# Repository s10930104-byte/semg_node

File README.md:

Phase 1：需求收斂與競品拆解（本週優先）
明確定義系統需求：確立量測應用場景、通道數、取樣率、電池容量與目標續航時間，作為後續元件選型的唯一依據。

競品採購與拆解參考：視需求採購市售同類模組（如淘寶現成方案）進行拆解，分析其晶片配置與機構空間規劃（註：僅作架構參考，須依自身專案用途篩選，避免盲目照抄）。

Phase 2：核心硬體架構定案（MCU / BLE / IMU）
MCU 與 BLE 架構拍板：依運算需求與功耗預算，決定採用「BLE SoC 單晶片方案」或「獨立 MCU + 獨立 BLE 模組」。

通訊介面與腳位盤點 (Pinout)：確認 MCU 具備足夠通道數與硬體協議（SPI / I2C / UART / SWD），確保能同時掛載 ADS1292、IMU 與燒錄除錯介面而不衝突。

IMU 感測器選型：確認慣性測量單元型號與通訊介面（SPI 或 I2C），完成硬體規格鎖定（韌體演算法待硬體定案後再行開發）。

Phase 3：電源管理與類比前端規劃（Power & AFE）
電源控制器與 S0–S5 狀態機設計：選定 PMIC / 充放電管理 IC，並定義 S0（全速運作）至 S5（完全關機斷電）各階段的供電策略與喚醒條件。

LDO 電源軌配置 (Power Tree)：

規劃 小電流低雜訊 LDO 專供類比前端（ADS1292），確保訊號品質。

規劃 大電流 LDO 供應數位主控與 IMU 等高功耗周邊。

確認其餘次要邏輯電源直接沿用 BLE 模組內建 LDO（若 Phase 2 改採單晶片方案則統一由上述兩顆分配）。

ADS1292 前端防護修改：將輸入端靜電保護（ESD）改為類比訊號專用規格（低漏電流、低寄生電容），避免影響微弱生理訊號。

Phase 4：機構介面與人機互動確認（開板前 Final Check）
雙模式電極介面定案：

確認板端/外殼乾式電極接觸點配置。

選定外接導線 Connector 規格，支援拉線外接標準貼片式 ECG/EMG 電極。

自定義按鍵 (User Button) 配置：預留實體按鍵並接至具備中斷喚醒功能的 MCU GPIO，供後期韌體自定義功能（開關機、配對、事件標記等）。

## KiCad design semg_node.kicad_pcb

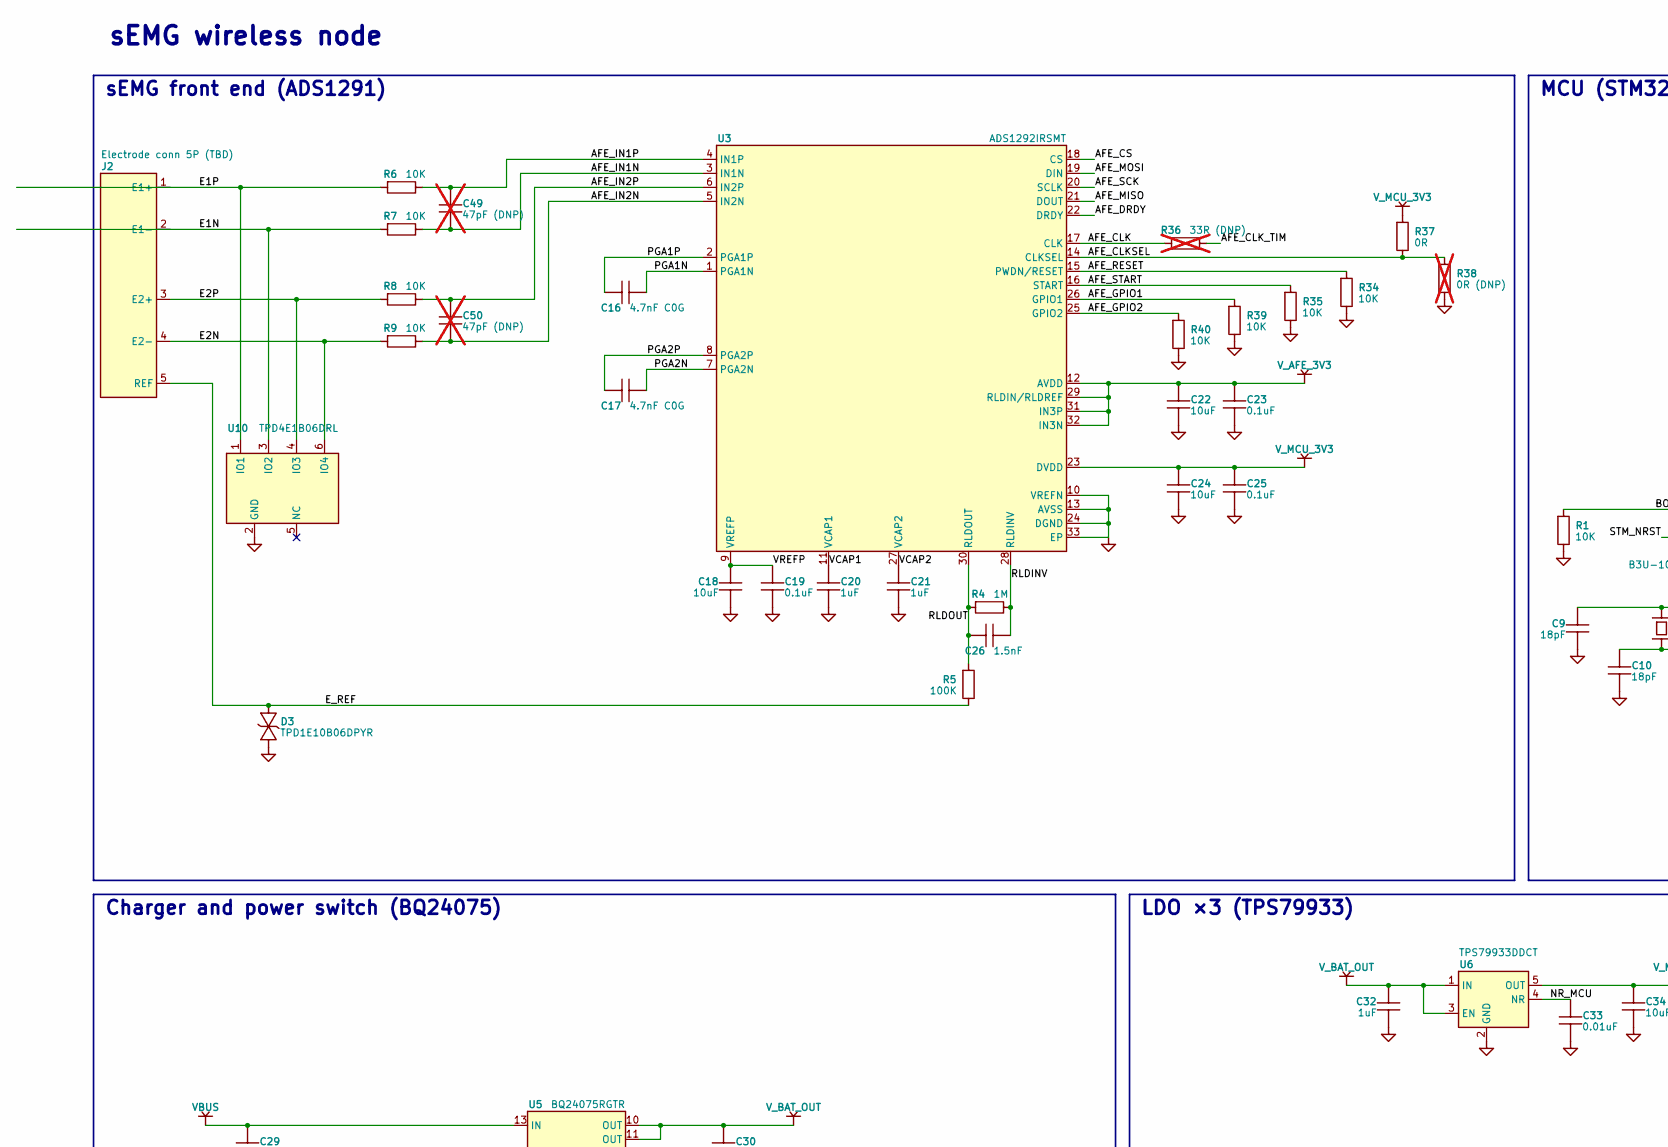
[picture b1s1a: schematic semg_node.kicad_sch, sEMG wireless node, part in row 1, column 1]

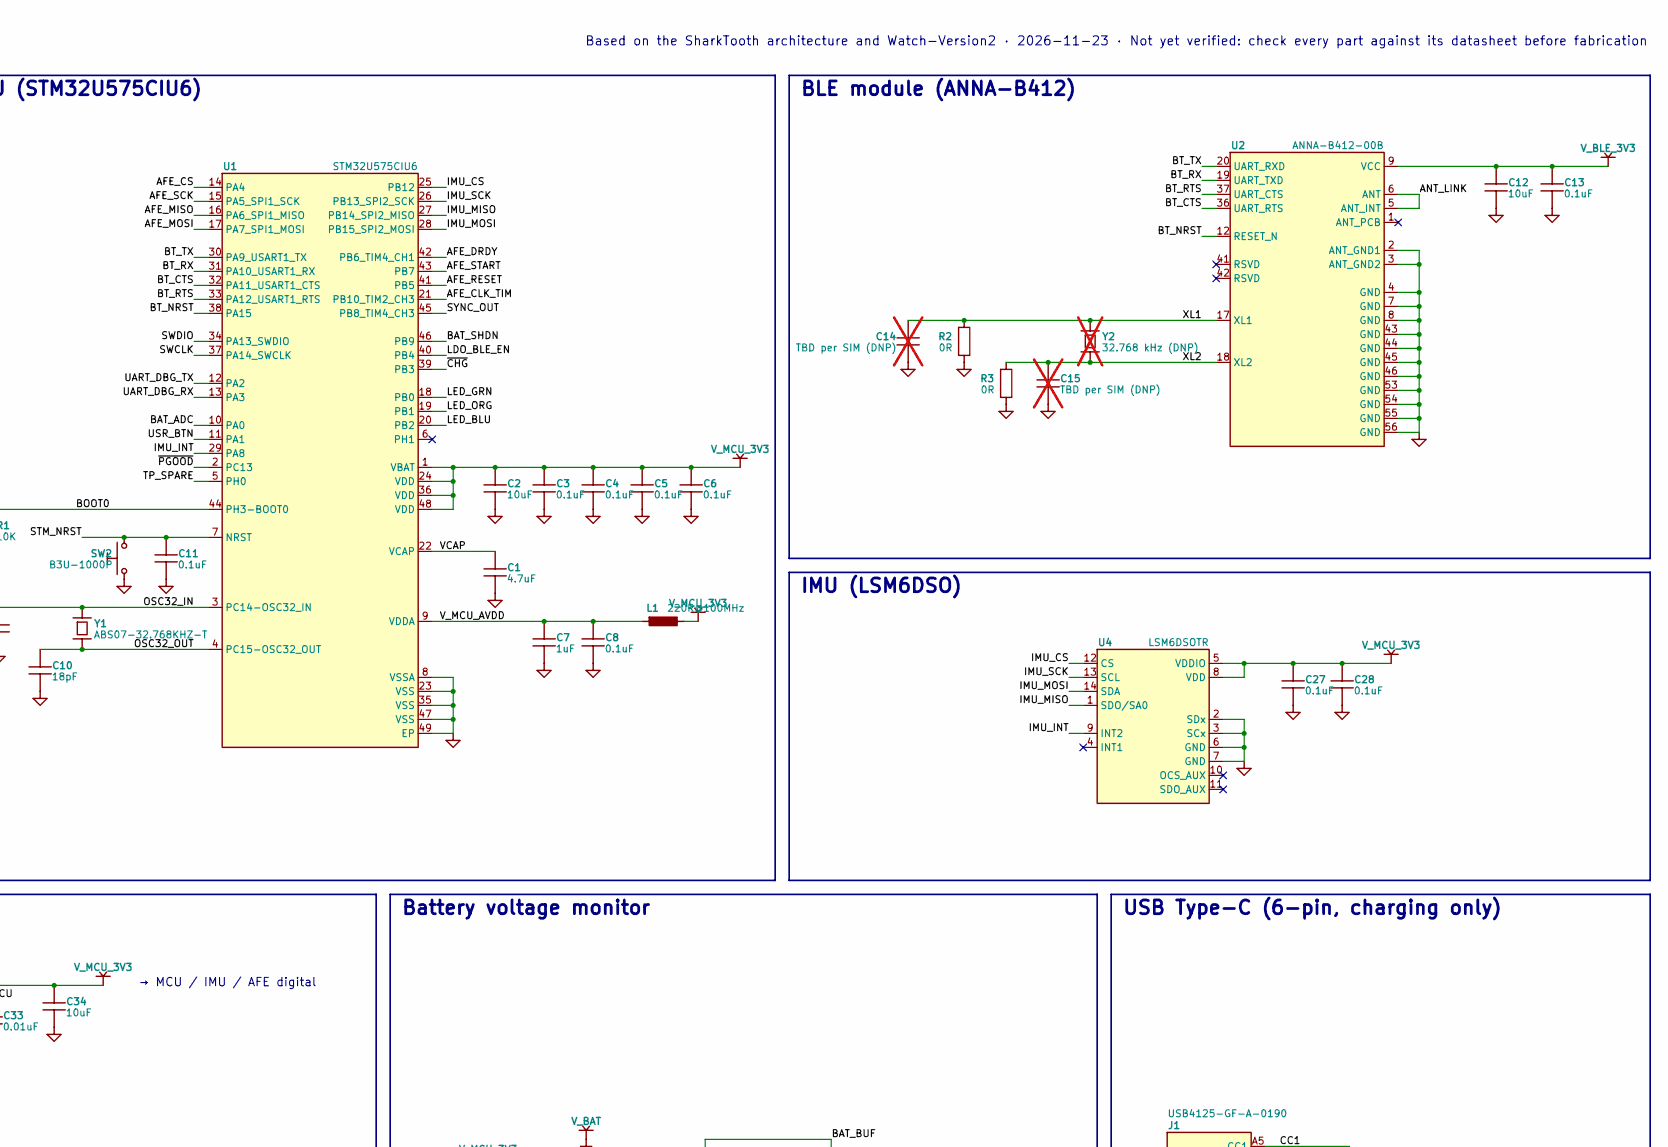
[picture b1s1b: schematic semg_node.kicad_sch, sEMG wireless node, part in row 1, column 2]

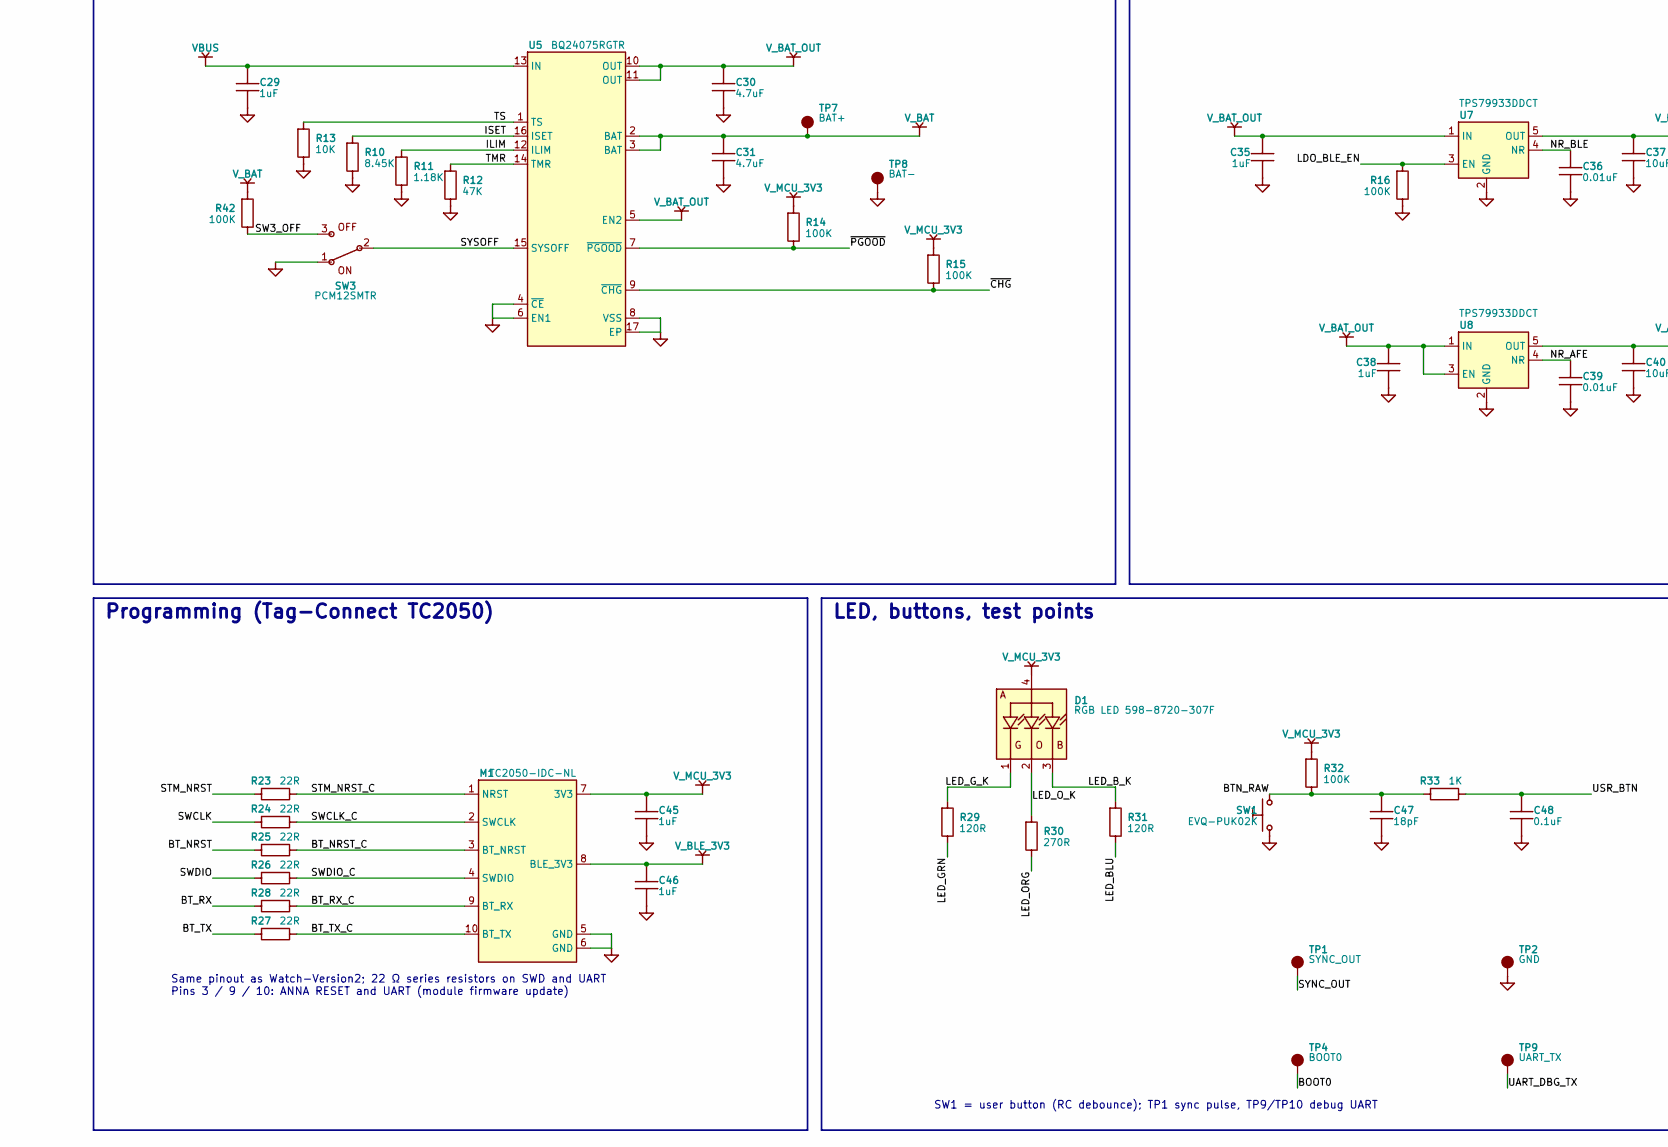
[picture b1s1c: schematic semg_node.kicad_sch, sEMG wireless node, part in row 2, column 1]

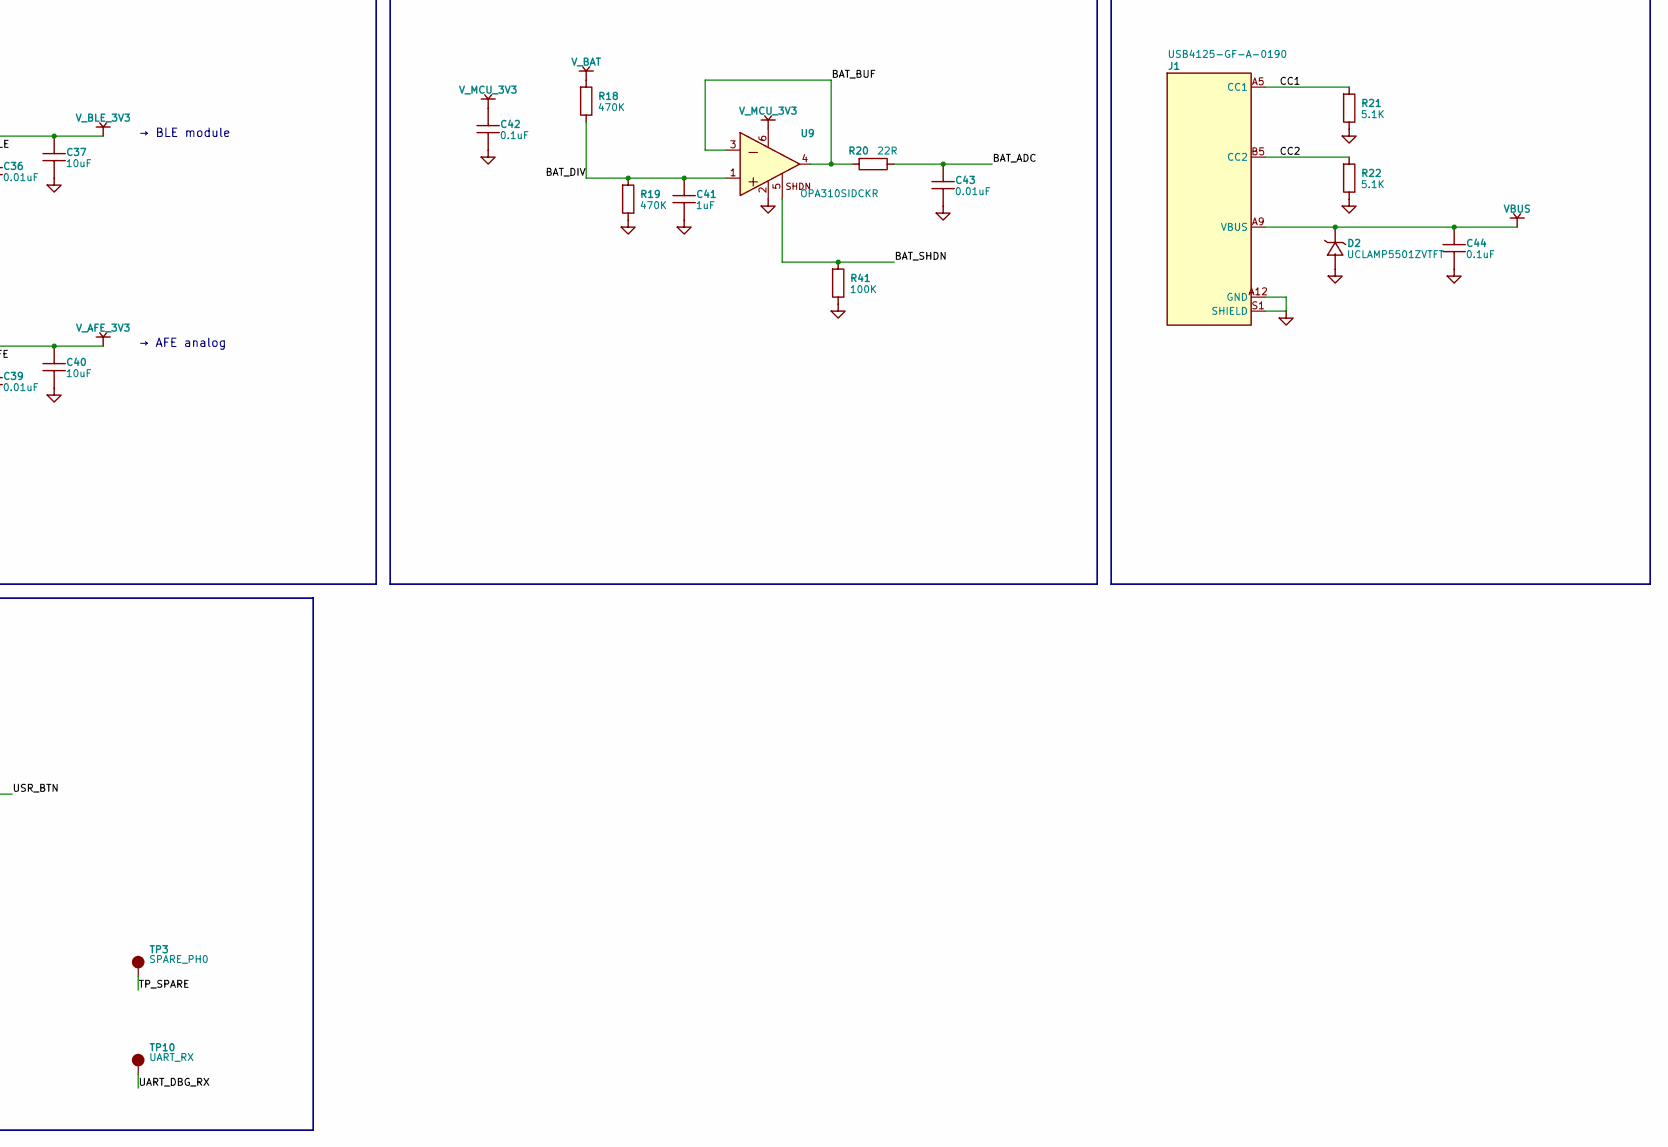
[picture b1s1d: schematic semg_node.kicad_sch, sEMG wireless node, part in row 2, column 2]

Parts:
C1, C30, C31: 4.7uF; C_0603_1608Metric
C2, C12, C18, C22, C24, C34, C37, C40: 10uF; C_0603_1608Metric
C3, C4, C5, C6, C8, C11, C13, C19, C23, C25, C27, C28, C42, C44, C48: 0.1uF; C_0402_1005Metric
C7, C20, C21, C29, C32, C35, C38, C41, C45, C46: 1uF; C_0402_1005Metric
C9, C10, C47: 18pF; C_0402_1005Metric
C14, C15: TBD per SIM (DNP); C_0402_1005Metric; not fitted
C16, C17: 4.7nF C0G; C_0402_1005Metric
C26: 1.5nF; C_0402_1005Metric
C33, C36, C39, C43: 0.01uF; C_0402_1005Metric
C49, C50: 47pF (DNP); C_0402_1005Metric; not fitted
D1: RGB LED 598-8720-307F; LED_RGB_Wuerth-PLCC4_3.2x2.8mm_150141M173100
D2: UCLAMP5501ZVTFT; D_SOD-882
D3: TPD1E10B06DPYR; D_SOD-882
J1: USB4125-GF-A-0190; USB_C_Receptacle_GCT_USB4125-xx-x-0190_6P_TopMnt_Horizontal
J2: Electrode conn 5P (TBD); JST_SH_SM05B-SRSS-TB_1x05-1MP_P1.00mm_Horizontal
L1: 220R@100MHz; L_0402_1005Metric
M1: TC2050-IDC-NL; Tag-Connect_TC2050-IDC-NL_2x05_P1.27mm_Vertical
R1, R6, R7, R8, R9, R13, R34, R35, R39, R40: 10K; R_0402_1005Metric
R2, R3, R37: 0R; R_0402_1005Metric
R4: 1M; R_0402_1005Metric
R5: 100K; R_0603_1608Metric
R10: 8.45K; R_0402_1005Metric
R11: 1.18K; R_0402_1005Metric
R12: 47K; R_0402_1005Metric
R14, R15, R16, R32, R41, R42: 100K; R_0402_1005Metric
R18, R19: 470K; R_0402_1005Metric
R20, R23, R24, R25, R26, R27, R28: 22R; R_0402_1005Metric
R21, R22: 5.1K; R_0402_1005Metric
R29, R31: 120R; R_0402_1005Metric
R30: 270R; R_0402_1005Metric
R33: 1K; R_0402_1005Metric
R36: 33R (DNP); R_0402_1005Metric; not fitted
R38: 0R (DNP); R_0402_1005Metric; not fitted
SW1: EVQ-PUK02K; Panasonic_EVQPUK_EVQPUB
SW2: B3U-1000P; SW_SPST_B3U-1000P
SW3: PCM12SMTR; SW_SPDT_PCM12
TP1: SYNC_OUT; TestPoint_Pad_D1.0mm
TP2: GND; TestPoint_Pad_D1.0mm
TP3: SPARE_PH0; TestPoint_Pad_D1.0mm
TP4: BOOT0; TestPoint_Pad_D1.0mm
TP7: BAT+; TestPoint_Pad_1.5x1.5mm
TP8: BAT-; TestPoint_Pad_1.5x1.5mm
TP9: UART_TX; TestPoint_Pad_D1.0mm
TP10: UART_RX; TestPoint_Pad_D1.0mm
U1: STM32U575CIU6; QFN-48-1EP_7x7mm_P0.5mm_EP5.6x5.6mm
U2: ANNA-B412-00B
U3: ADS1292IRSMT; VQFN-32-1EP_4x4mm_P0.4mm_EP2.8x2.8mm
U4: LSM6DSOTR; LGA-14_3x2.5mm_P0.5mm_LayoutBorder3x4y
U5: BQ24075RGTR; QFN-16-1EP_3x3mm_P0.5mm_EP1.7x1.7mm
U6, U7, U8: TPS79933DDCT; SOT-23-5
U9: OPA310SIDCKR; SOT-363_SC-70-6
U10: TPD4E1B06DRL; SOT-563
Y1: ABS07-32.768KHZ-T; Crystal_SMD_3215-2Pin_3.2x1.5mm
Y2: 32.768 kHz (DNP); Crystal_SMD_3215-2Pin_3.2x1.5mm; not fitted

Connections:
AFE_CLK: R36.2, U3.17 (CLK)
AFE_CLKSEL: R37.1, R38.1, U3.14 (CLKSEL)
AFE_CLK_TIM: R36.1, U1.21 (PB10_TIM2_CH3)
AFE_CS: U1.14 (PA4), U3.18 (CS)
AFE_DRDY: U1.42 (PB6_TIM4_CH1), U3.22 (DRDY)
AFE_GPIO1: R39.1, U3.26 (GPIO1)
AFE_GPIO2: R40.1, U3.25 (GPIO2)
AFE_IN1N: C49.2, R7.2, U3.3 (IN1N)
AFE_IN1P: C49.1, R6.2, U3.4 (IN1P)
AFE_IN2N: C50.2, R9.2, U3.5 (IN2N)
AFE_IN2P: C50.1, R8.2, U3.6 (IN2P)
AFE_MISO: U1.16 (PA6_SPI1_MISO), U3.21 (DOUT)
AFE_MOSI: U1.17 (PA7_SPI1_MOSI), U3.19 (DIN)
AFE_RESET: R34.1, U1.41 (PB5), U3.15 (PWDN/RESET)
AFE_SCK: U1.15 (PA5_SPI1_SCK), U3.20 (SCLK)
AFE_START: R35.1, U1.43 (PB7), U3.16 (START)
BAT_ADC: C43.1, R20.2, U1.10 (PA0)
BAT_BUF: R20.1, U9.3 (-IN), U9.4 (OUT)
BAT_DIV: C41.1, R18.2, R19.1, U9.1 (+IN)
BAT_SHDN: R41.1, U1.46 (PB9), U9.5 (SHDN)
BOOT0: R1.1, TP4.1, U1.44 (PH3-BOOT0)
BTN_RAW: C47.1, R32.2, R33.1, SW1.2
BT_CTS: U1.32 (PA11_USART1_CTS), U2.36 (UART_RTS)
BT_NRST: R25.1, U1.38 (PA15), U2.12 (RESET_N)
BT_NRST_C: M1.3 (BT_NRST), R25.2
BT_RTS: U1.33 (PA12_USART1_RTS), U2.37 (UART_CTS)
BT_RX: R28.1, U1.31 (PA10_USART1_RX), U2.19 (UART_TXD)
BT_RX_C: M1.9 (BT_RX), R28.2
BT_TX: R27.1, U1.30 (PA9_USART1_TX), U2.20 (UART_RXD)
BT_TX_C: M1.10 (BT_TX), R27.2
CC1: J1.A5 (CC1), R21.1
CC2: J1.B5 (CC2), R22.1
E1N: J2.2 (E1-), R7.1, U10.3 (IO2)
E1P: J2.1 (E1+), R6.1, U10.1 (IO1)
E2N: J2.4 (E2-), R9.1, U10.6 (IO4)
E2P: J2.3 (E2+), R8.1, U10.4 (IO3)
E_REF: D3.1, J2.5 (REF), R5.2
GND: C1.2, C2.2, C3.2, C4.2, C5.2, C6.2, C7.2, C8.2, C9.2, C10.2, C11.2, C12.2, C13.2, C14.2, C15.2, C18.2, C19.2, C20.2, C21.2, C22.2, C23.2, C24.2, C25.2, C27.2, C28.2, C29.2, C30.2, C31.2, C32.2, C33.2, C34.2, C35.2, C36.2, C37.2, C38.2, C39.2, C40.2, C41.2, C42.2, C43.2, C44.2, C45.2, C46.2, C47.2, C48.2, D2.2, D3.2, J1.A12 (GND), J1.B12 (GND), J1.S1 (SHIELD), M1.5 (GND), M1.6 (GND), R1.2, R2.2, R3.2, R10.2, R11.2, R12.2, R13.2, R16.2, R19.2, R21.2, R22.2, R34.2, R35.2, R38.2, R39.2, R40.2, R41.2, SW1.1, SW2.2, SW3.1 (ON), TP2.1, TP8.1, U1.8 (VSSA), U1.23 (VSS), U1.35 (VSS), U1.47 (VSS), U1.49 (EP), U2.2 (ANT_GND1), U2.3 (ANT_GND2), U2.4 (GND), U2.7 (GND), U2.8 (GND), U2.43 (GND), U2.44 (GND), U2.45 (GND), U2.46 (GND), U2.53 (GND), U2.54 (GND), U2.55 (GND), U2.56 (GND), U3.10 (VREFN), U3.13 (AVSS), U3.24 (DGND), U3.33 (EP), U4.2 (SDx), U4.3 (SCx), U4.6 (GND), U4.7 (GND), U5.4 (~CE), U5.6 (EN1), U5.8 (VSS), U5.17 (EP), U6.2 (GND), U7.2 (GND), U8.2 (GND), U9.2 (V-), U10.2 (GND)
ILIM: R11.1, U5.12 (ILIM)
IMU_CS: U1.25 (PB12), U4.12 (CS)
IMU_INT: U1.29 (PA8), U4.9 (INT2)
IMU_MISO: U1.27 (PB14_SPI2_MISO), U4.1 (SDO/SA0)
IMU_MOSI: U1.28 (PB15_SPI2_MOSI), U4.14 (SDA)
IMU_SCK: U1.26 (PB13_SPI2_SCK), U4.13 (SCL)
ISET: R10.1, U5.16 (ISET)
LDO_BLE_EN: R16.1, U1.40 (PB4), U7.3 (EN)
LED_BLU: R31.1, U1.20 (PB2)
LED_B_K: D1.3 (B), R31.2
LED_GRN: R29.1, U1.18 (PB0)
LED_G_K: D1.1 (G), R29.2
LED_ORG: R30.1, U1.19 (PB1)
LED_O_K: D1.2 (O), R30.2
NR_AFE: C39.1, U8.4 (NR)
NR_BLE: C36.1, U7.4 (NR)
NR_MCU: C33.1, U6.4 (NR)
unnamed: U2.5 (ANT_INT), U2.6 (ANT)
OSC32_IN: C9.1, U1.3 (PC14-OSC32_IN), Y1.2
OSC32_OUT: C10.1, U1.4 (PC15-OSC32_OUT), Y1.1
PGA1N: C16.2, U3.1 (PGA1N)
PGA1P: C16.1, U3.2 (PGA1P)
PGA2N: C17.2, U3.7 (PGA2N)
PGA2P: C17.1, U3.8 (PGA2P)
RLDINV: C26.2, R4.2, U3.28 (RLDINV)
RLDOUT: C26.1, R4.1, R5.1, U3.30 (RLDOUT)
STM_NRST: C11.1, R23.1, SW2.1, U1.7 (NRST)
STM_NRST_C: M1.1 (NRST), R23.2
SW3_OFF: R42.2, SW3.3 (OFF)
SWCLK: R24.1, U1.37 (PA14_SWCLK)
SWCLK_C: M1.2 (SWCLK), R24.2
SWDIO: R26.1, U1.34 (PA13_SWDIO)
SWDIO_C: M1.4 (SWDIO), R26.2
SYNC_OUT: TP1.1, U1.45 (PB8_TIM4_CH3)
SYSOFF: SW3.2 (COM), U5.15 (SYSOFF)
TMR: R12.1, U5.14 (TMR)
TP_SPARE: TP3.1, U1.5 (PH0)
TS: R13.1, U5.1 (TS)
UART_DBG_RX: TP10.1, U1.13 (PA3)
UART_DBG_TX: TP9.1, U1.12 (PA2)
USR_BTN: C48.1, R33.2, U1.11 (PA1)
VBUS: C29.1, C44.1, D2.1, J1.A9 (VBUS), J1.B9 (VBUS), U5.13 (IN)
VCAP: C1.1, U1.22 (VCAP)
VCAP1: C20.1, U3.11 (VCAP1)
VCAP2: C21.1, U3.27 (VCAP2)
VREFP: C18.1, C19.1, U3.9 (VREFP)
V_AFE_3V3: C22.1, C23.1, C40.1, U3.12 (AVDD), U3.29 (RLDIN/RLDREF), U3.31 (IN3P), U3.32 (IN3N), U8.5 (OUT)
V_BAT: C31.1, R18.1, R42.1, TP7.1, U5.2 (BAT), U5.3 (BAT)
V_BAT_OUT: C30.1, C32.1, C35.1, C38.1, U5.5 (EN2), U5.10 (OUT), U5.11 (OUT), U6.1 (IN), U6.3 (EN), U7.1 (IN), U8.1 (IN), U8.3 (EN)
V_BLE_3V3: C12.1, C13.1, C37.1, C46.1, M1.8 (BLE_3V3), U2.9 (VCC), U7.5 (OUT)
V_MCU_3V3: C2.1, C3.1, C4.1, C5.1, C6.1, C24.1, C25.1, C27.1, C28.1, C34.1, C42.1, C45.1, D1.4 (A), L1.1, M1.7 (3V3), R14.2, R15.2, R32.1, R37.2, U1.1 (VBAT), U1.24 (VDD), U1.36 (VDD), U1.48 (VDD), U3.23 (DVDD), U4.5 (VDDIO), U4.8 (VDD), U6.5 (OUT), U9.6 (V+)
V_MCU_AVDD: C7.1, C8.1, L1.2, U1.9 (VDDA)
XL1: C14.1, R2.1, U2.17 (XL1), Y2.1
XL2: C15.1, R3.1, U2.18 (XL2), Y2.2
~CHG: R15.1, U1.39 (PB3), U5.9 (~CHG)
~PGOOD: R14.1, U1.2 (PC13), U5.7 (~PGOOD)

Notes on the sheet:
MCU (STM32U575CIU6)
BLE module (ANNA-B412)
→ BLE module
Battery voltage monitor
Charger and power switch (BQ24075)
IMU (LSM6DSO)
→ MCU / IMU / AFE digital
Same pinout as Watch-Version2; 22 Ω series resistors on SWD and UART Pins 3 / 9 / 10: ANNA RESET and UART (module firmware update)
LED, buttons, test points
sEMG wireless node
sEMG front end (ADS1291)
Programming (Tag-Connect TC2050)
→ AFE analog
SW1 = user button (RC debounce); TP1 sync pulse, TP9/TP10 debug UART
LDO ×3 (TPS79933)
USB Type-C (6-pin, charging only)
Based on the SharkTooth architecture and Watch-Version2 · 2026-11-23 · Not yet verified: check every part against its datasheet before fabrication

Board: 4 copper layers, 120 parts (72 on the bottom side), 91 nets, no tracks yet.
